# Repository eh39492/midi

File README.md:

I am making the Half-Life Week 3 starter project: MIDI
The PCB uses a custom capacitive key layout, a custom part layout, and customizations. The code also uses custom elements. The capacitive touch keys are in a hexagonal shape.
WHAT IT WILL DO:
When connected to a computer, it plays music and notes; the switches and potentiometers allow audio manipulation like volume and tone!

THE PCB desgin

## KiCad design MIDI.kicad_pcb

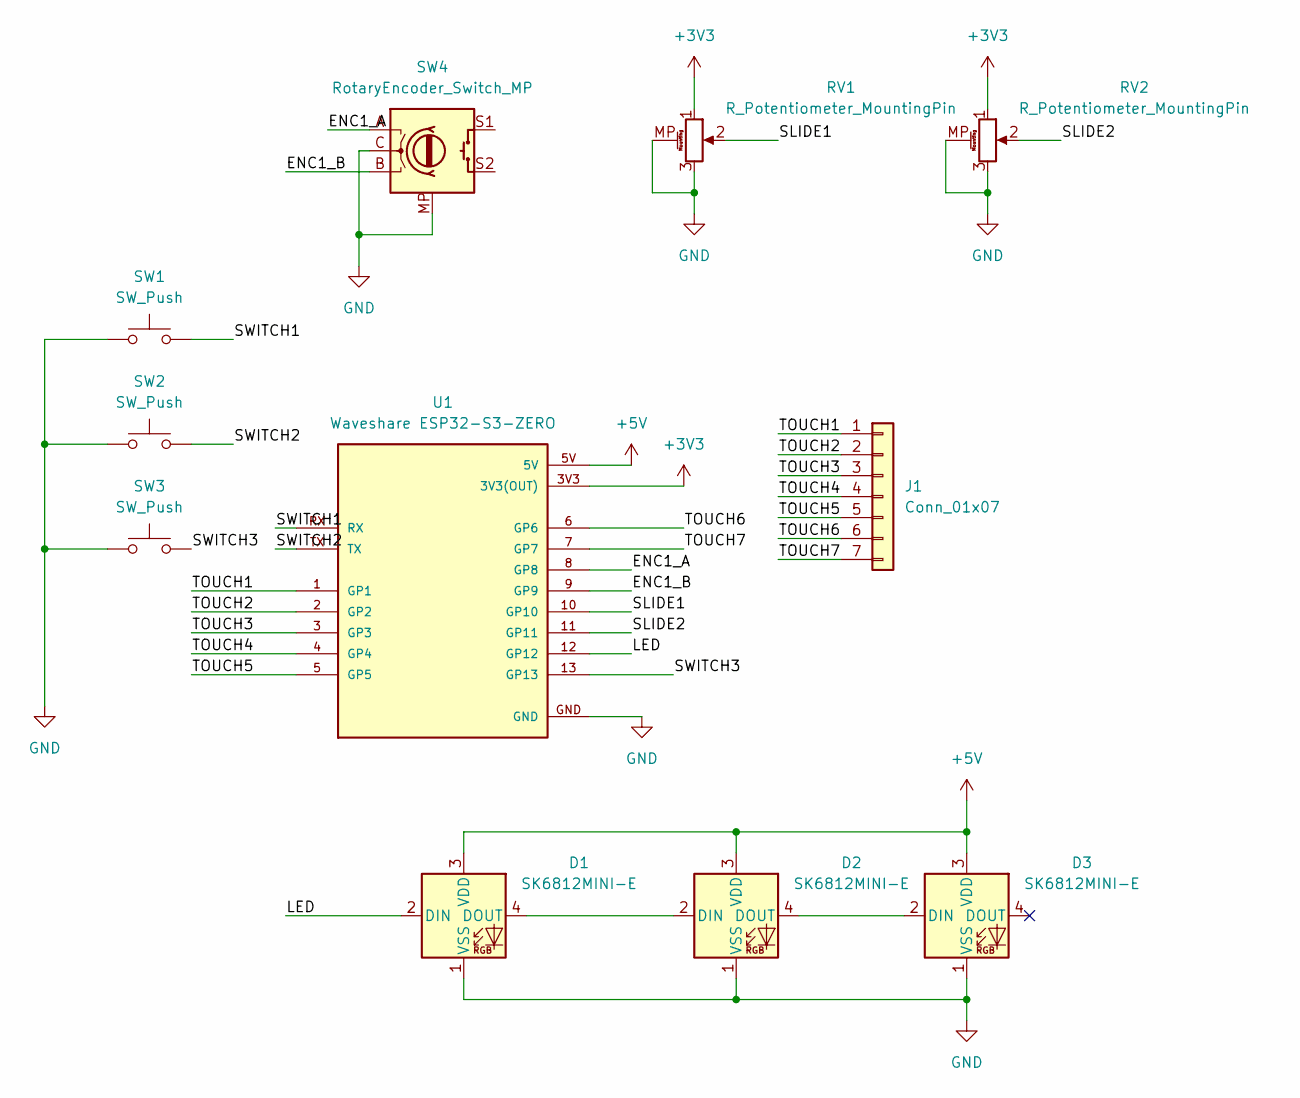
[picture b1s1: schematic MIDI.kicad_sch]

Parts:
D1, D2, D3: SK6812MINI-E; LED_SK6812MINI-E_3.2x2.8mm_P1.5mm_ReverseMount
J1: Conn_01x07; Untitled
RV1, RV2: R_Potentiometer_MountingPin; Potentiometer_Bourns_PTA1543_Single_Slide
SW1, SW2, SW3: SW_Push; Kailh Choc Low-Profile Switches
SW4: RotaryEncoder_Switch_MP; RotaryEncoder_Alps_EC11E-Switch_Vertical_H20mm
U1: Waveshare ESP32-S3-ZERO; Waveshare ESP32-S3-Zero; PARTREV NA

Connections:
+3V3: RV1.1, RV2.1, U1.3V3 (3V3(OUT))
+5V: D1.3 (VDD), D2.3 (VDD), D3.3 (VDD), U1.5V
/ENC1_A: SW4.A, U1.8 (GP8)
/ENC1_B: SW4.B, U1.9 (GP9)
/LED: D1.2 (DIN), U1.12 (GP12)
/SLIDE1: RV1.2, U1.10 (GP10)
/SLIDE2: RV2.2, U1.11 (GP11)
/SWITCH1: SW1.2, U1.RX
/SWITCH2: SW2.2, U1.TX
/SWITCH3: SW3.2, U1.13 (GP13)
/TOUCH1: J1.1, U1.1 (GP1)
/TOUCH2: J1.2, U1.2 (GP2)
/TOUCH3: J1.3, U1.3 (GP3)
/TOUCH4: J1.4, U1.4 (GP4)
/TOUCH5: J1.5, U1.5 (GP5)
/TOUCH6: J1.6, U1.6 (GP6)
/TOUCH7: J1.7, U1.7 (GP7)
GND: D1.1 (VSS), D2.1 (VSS), D3.1 (VSS), RV1.3, RV1.MP (MountPin), RV2.3, RV2.MP (MountPin), SW1.1, SW2.1, SW3.1, SW4.C, SW4.MP, U1.GND
unnamed: D1.4 (DOUT), D2.2 (DIN)
unnamed: D2.4 (DOUT), D3.2 (DIN)

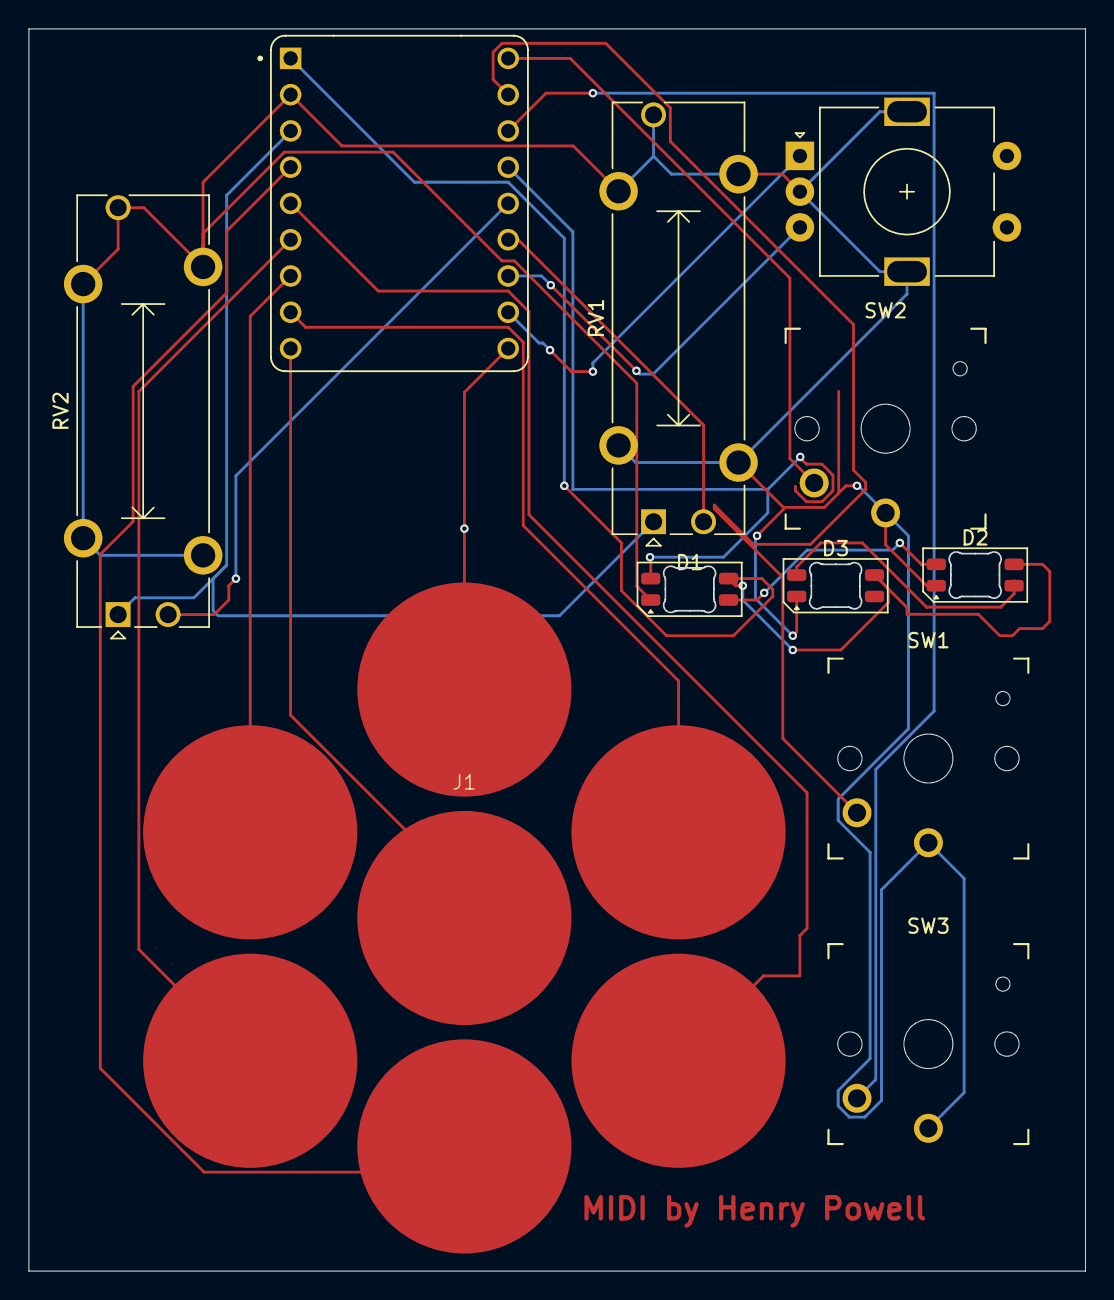
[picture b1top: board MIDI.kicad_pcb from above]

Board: 2 copper layers, 74.0 x 87.0 mm, 11 parts (0 on the bottom side), 20 nets.

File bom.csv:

Designator,Footprint,Quantity,Value,LCSC Part #
"D1, D2, D3",LED_SK6812MINI-E_3.2x2.8mm_P1.5mm_ReverseMount,3,SK6812MINI-E,
J1,Untitled,1,Conn_01x07,
"RV1, RV2",Potentiometer_Bourns_PTA1543_Single_Slide,2,R_Potentiometer_MountingPin,
"SW1, SW2, SW3",Kailh Choc Low-Profile Switches,3,SW_Push,
SW4,RotaryEncoder_Alps_EC11E-Switch_Vertical_H20mm,1,RotaryEncoder_Switch_MP,
U1,Waveshare ESP32-S3-Zero,1,Waveshare ESP32-S3-ZERO,
